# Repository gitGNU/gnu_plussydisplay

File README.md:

# Plussy Display Introduction

This repository contains free software and hardware design components for a small LED matrix resembling FSFE's plussy mascot. It is intended to be used, e.g., as an eyecatcher for fellowship events.

## License Information

All files in this project (except some configuration files where stated in their header) are licensed under the GPLv3 license as stated in the next section (GPLv3 License Statement).

## GPLv3 License Statement

Plussy Display
Copyright (C) 2015  Christian Carlowitz <chca@cmesh.de>

This program is free software: you can redistribute it and/or modify
it under the terms of the GNU General Public License as published by
the Free Software Foundation, either version 3 of the License, or
(at your option) any later version.

This program is distributed in the hope that it will be useful,
but WITHOUT ANY WARRANTY; without even the implied warranty of
MERCHANTABILITY or FITNESS FOR A PARTICULAR PURPOSE.  See the
GNU General Public License for more details.

You should have received a copy of the GNU General Public License
along with this program.  If not, see <http://www.gnu.org/licenses/>.

# Usage
## Adding new animations

* install dependencies for simulator (gcc, make, python2.7 including development headers, python-pygame)
* add new animation file in _uc/src/animations_, e.g., by copying an existing file
* rename animation function to match file name
* register animation function in _common.h_ for microcontroller (add declaration and _animTable_ entry)
* run `make ANIM=anim_funcname` in folder _sim_ to test

## Compiling microcontroller code

* install dependencies (gcc-arm-embedded from https://launchpad.net/gcc-arm-embedded, openocd, make)
* get libopencm3 (run `git submodule init`, enter _uc/libopencm3_, run `make`)
* run `make` or `make V=1` (verbose) in folder _uc_

## Flashing microcontroller

* find out openocd name for your JTAG adapter
* change parameter _OOCD_INTERFACE_ in file _uc/libopencm3.target.mk_ accordingly
* run `make flash` or `make flash V=1` (verbose) in folder _uc_

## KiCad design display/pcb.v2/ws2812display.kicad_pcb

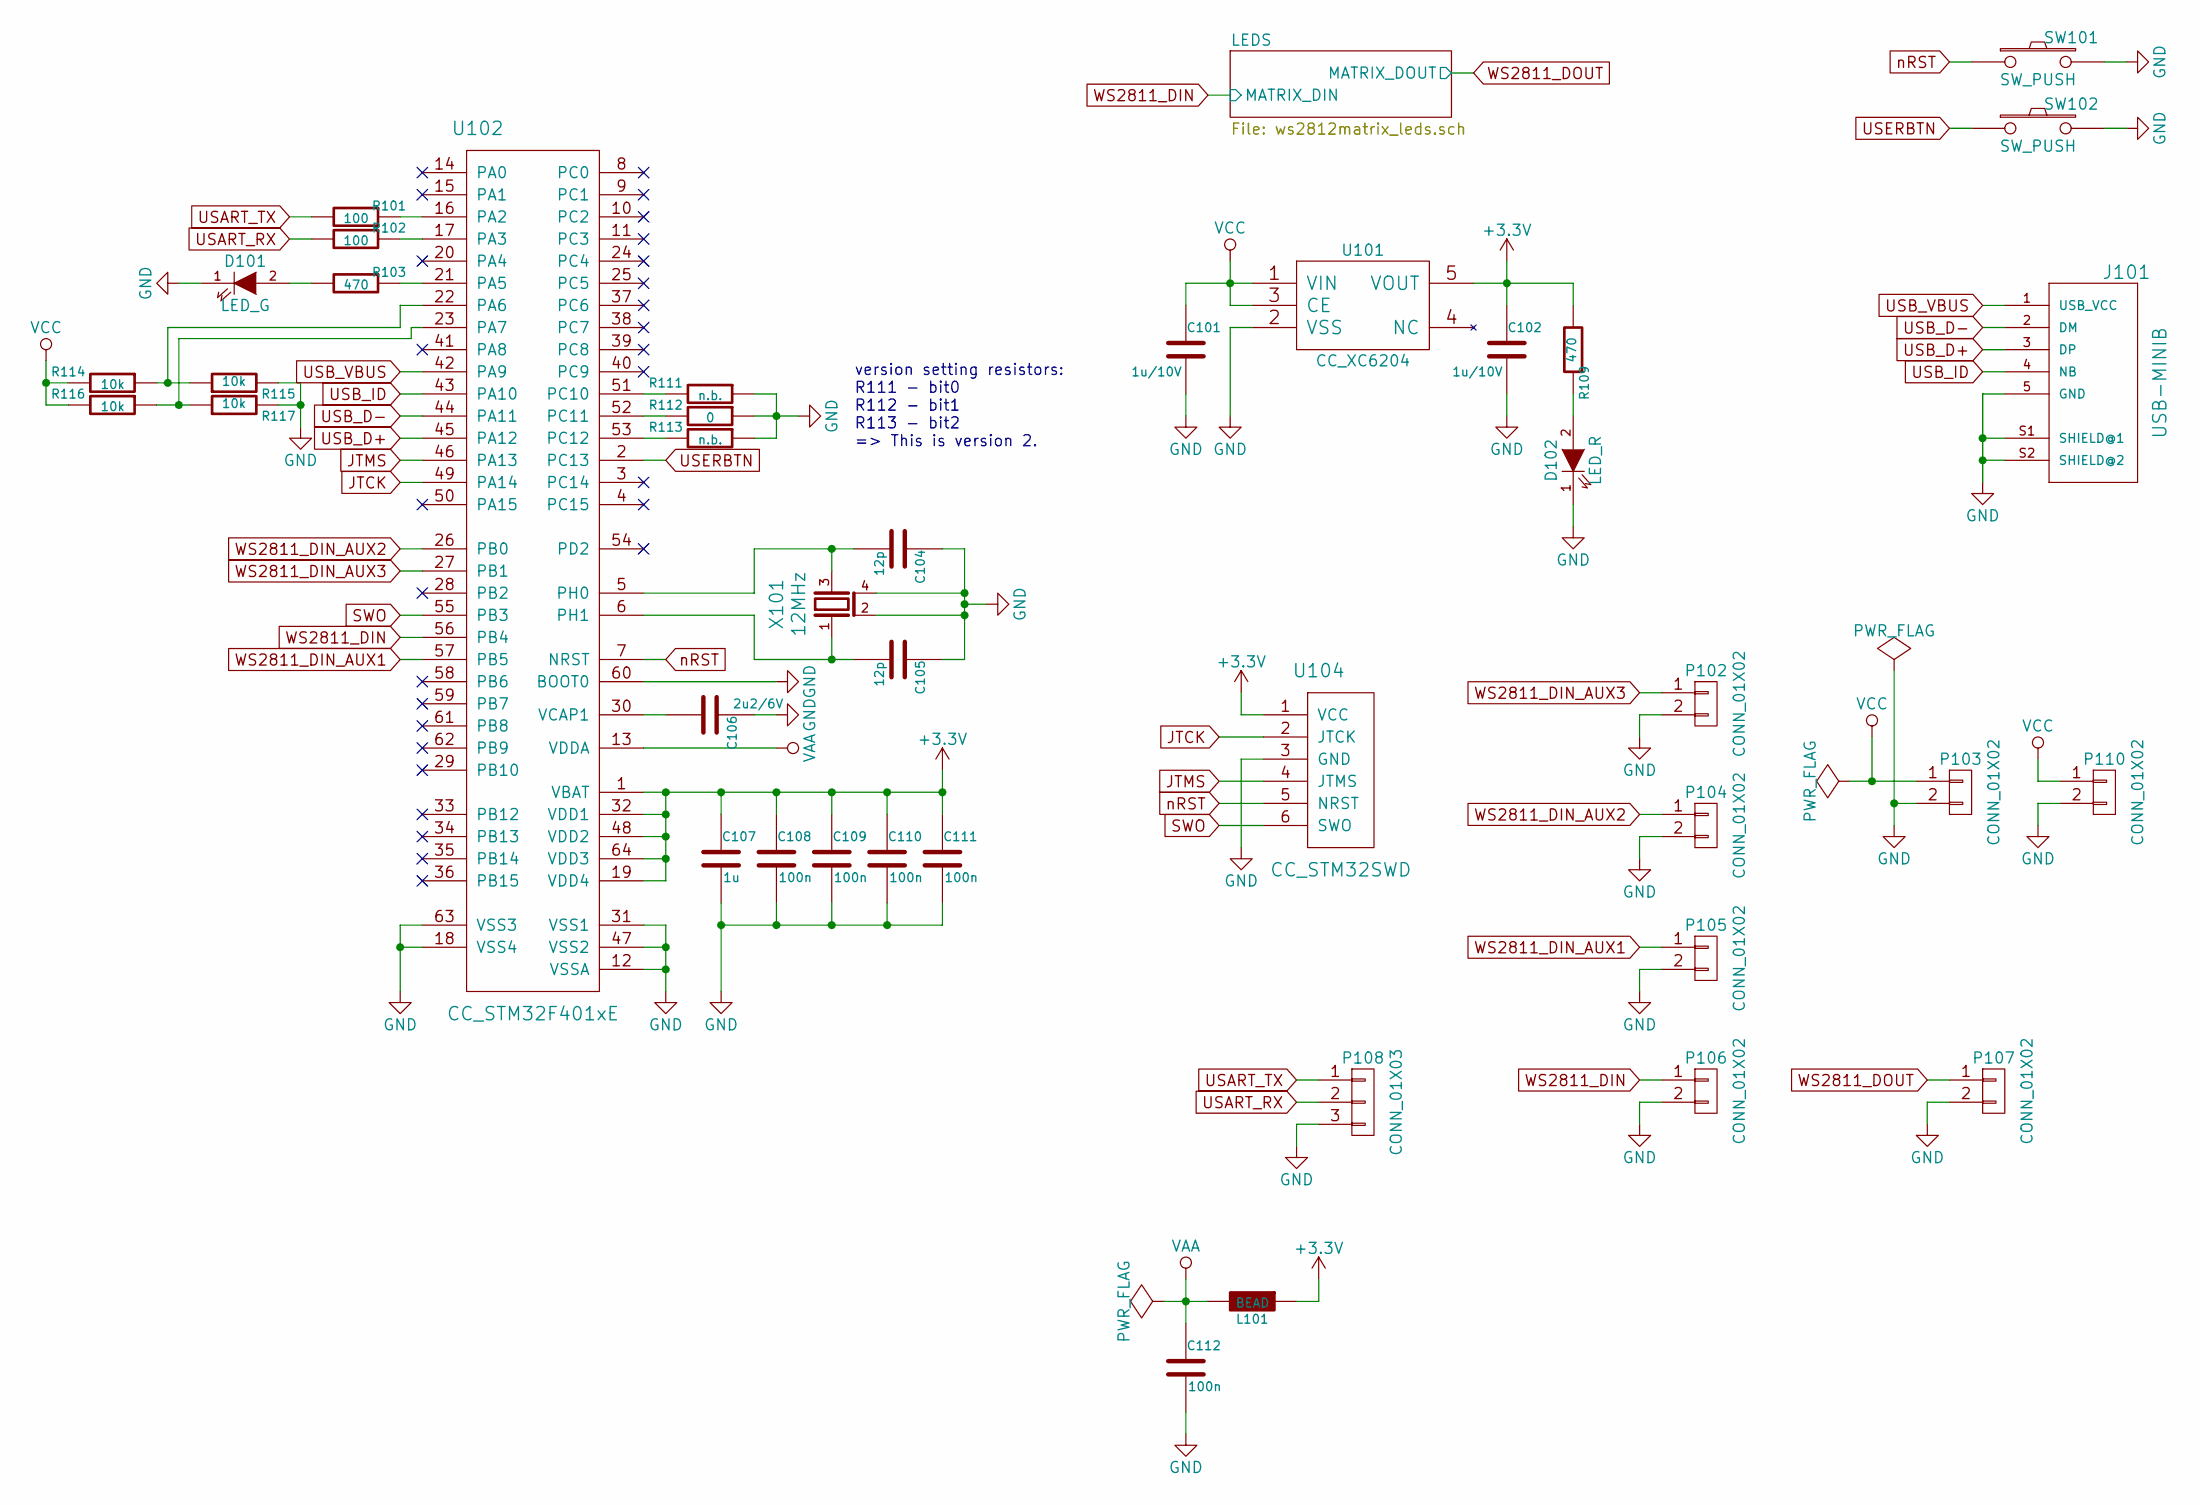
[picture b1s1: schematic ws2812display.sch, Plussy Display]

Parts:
C101, C102: 1u/10V; rcl-cc-0603
C104, C105: 12p; rcl-cc-0603
C106: 2u2/6V; rcl-cc-0603
C107: 1u; rcl-cc-0603
C108, C109, C110, C111, C112: 100n; rcl-cc-0603
D101: LED_G; LED-0603
D102: LED_R; LED-0603
J101: USB-MINIB; con-usb-USB-B-MINI-THD
L101: BEAD; rcl-cc-0603
P102, P104, P105, P106, P107: CONN_01X02; Pin_Header_Straight_1x02
P103, P110: CONN_01X02; con-ria-TYPE_230_249_2PIN
P108: CONN_01X03; Pin_Header_Straight_1x03
R101, R102: 100; rcl-cc-0603
R103, R109: 470; rcl-cc-0603
R111, R113: n.b.; rcl-cc-0603
R112: 0; rcl-cc-0603
R114, R115, R116, R117: 10k; rcl-cc-0603
SW101, SW102: SW_PUSH; TASTER_3305B
U101: CC_XC6204; SOT23-5
U102: CC_STM32F401xE; lqfp64
U104: CC_STM32SWD; Pin_Header_Straight_1x06
X101: 12MHz; Q_EUROQUARTZ_MJ_3x5x1

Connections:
+3V3: C102.1, C107.1, C108.1, C109.1, C110.1, C111.1, L101.1, R109.2, U101.5 (VOUT), U102.1 (VBAT), U102.19 (VDD4), U102.32 (VDD1), U102.48 (VDD2), U102.64 (VDD3), U104.1 (VCC)
GND: C101.2, C102.2, C104.1, C105.1, C106.1, C107.2, C108.2, C109.2, C110.2, C111.2, C112.2, D101.1 (K), D102.1 (K), J101.5 (GND), J101.S1 (SHIELD@1), J101.S2 (SHIELD@2), P102.2, P103.2, P104.2, P105.2, P106.2, P107.2, P108.3, P110.2, R111.1, R112.1, R113.1, R115.2, R117.2, SW101.2, SW102.2, U101.2 (VSS), U102.12 (VSSA), U102.18 (VSS4), U102.31 (VSS1), U102.47 (VSS2), U102.60 (BOOT0), U102.63 (VSS3), U104.3 (GND), X101.2 (GND), X101.4 (GND); also elsewhere on the board
JTCK: U102.49 (PA14), U104.2 (JTCK)
JTMS: U102.46 (PA13), U104.4 (JTMS)
unnamed: C104.2, U102.5 (PH0), X101.3
unnamed: C105.2, U102.6 (PH1), X101.1
unnamed: C106.2, U102.30 (VCAP1)
unnamed: D101.2 (A), R103.2
unnamed: D102.2 (A), R109.1
unnamed: R101.1, U102.16 (PA2)
unnamed: R102.1, U102.17 (PA3)
unnamed: R103.1, U102.21 (PA5)
unnamed: R111.2, U102.51 (PC10)
unnamed: R112.2, U102.52 (PC11)
unnamed: R113.2, U102.53 (PC12)
unnamed: R114.1, R115.1, U102.22 (PA6)
unnamed: R116.1, R117.1, U102.23 (PA7)
SWO: U102.55 (PB3), U104.6 (SWO)
USART_RX: P108.2, R102.2
USART_TX: P108.1, R101.2
USB_D+: J101.3 (DP), U102.45 (PA12)
USB_D-: J101.2 (DM), U102.44 (PA11)
USB_ID: J101.4 (NB), U102.43 (PA10)
USB_VBUS: J101.1 (USB_VCC), U102.42 (PA9)
USERBTN: SW102.1, U102.2 (PC13)
VAA: C112.1, L101.2, U102.13 (VDDA)
VCC: C101.1, P103.1, P110.1, R114.2, R116.2, U101.1 (VIN), U101.3 (CE); also elsewhere on the board
WS2811_DIN: P106.1, U102.56 (PB4); also elsewhere on the board
WS2811_DIN_AUX1: P105.1, U102.57 (PB5)
WS2811_DIN_AUX2: P104.1, U102.26 (PB0)
WS2811_DIN_AUX3: P102.1, U102.27 (PB1)
WS2811_DOUT: P107.1; also elsewhere on the board
nRST: SW101.1, U102.7 (NRST), U104.5 (NRST)

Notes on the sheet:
version setting resistors: R111 - bit0 R112 - bit1 R113 - bit2 => This is version 2.

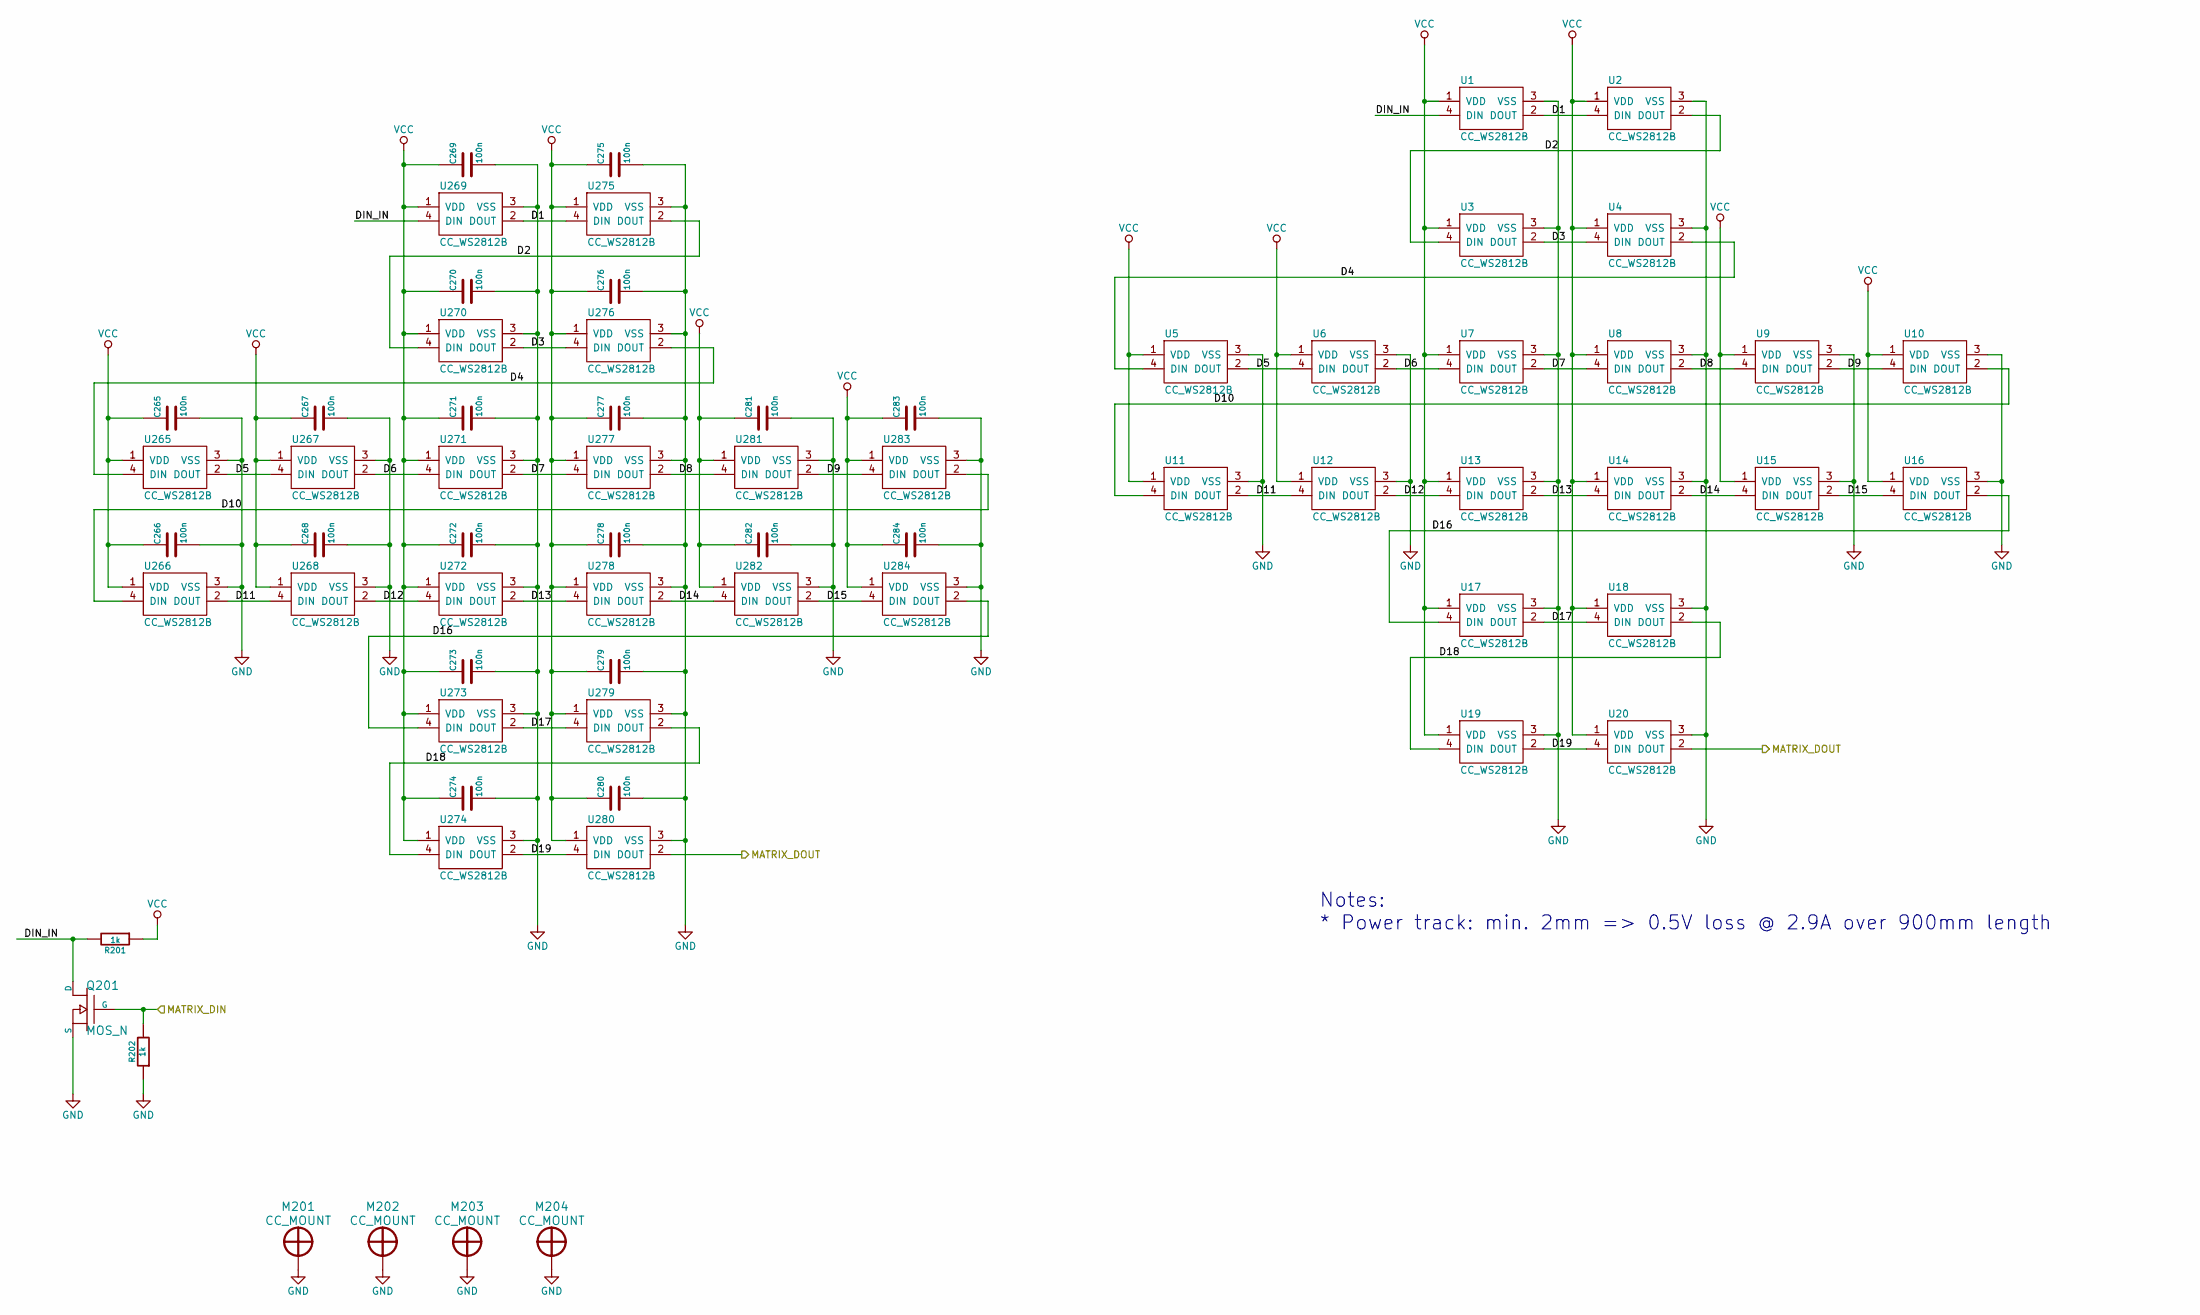
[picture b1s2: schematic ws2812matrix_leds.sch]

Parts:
C265, C266, C267, C268, C269, C270, C271, C272, C273, C274, C275, C276, C277, C278, C279, C280, C281, C282, C283, C284: 100n; rcl-cc-0603
M201, M202, M203, M204: CC_MOUNT; CC_MOUNT_PLATED_M3
Q201: MOS_N; CC_SOT23_MOS1
R201, R202: 1k; rcl-cc-0603
U1, U2, U3, U4, U5, U6, U7, U8, U9, U10, U11, U12, U13, U14, U15, U16, U17, U18, U19, U20: CC_WS2812B; WS2812B
U265, U266, U267, U268, U269, U270, U271, U272, U273, U274, U275, U276, U277, U278, U279, U280, U281, U282, U283, U284: CC_WS2812B; WS2812B_DUAL

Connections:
/LEDS/D1: U1.2 (DOUT), U2.4 (DIN), U269.2 (DOUT), U275.4 (DIN)
/LEDS/D2: U2.2 (DOUT), U3.4 (DIN), U270.4 (DIN), U275.2 (DOUT)
/LEDS/D3: U3.2 (DOUT), U4.4 (DIN), U270.2 (DOUT), U276.4 (DIN)
/LEDS/D4: U4.2 (DOUT), U5.4 (DIN), U265.4 (DIN), U276.2 (DOUT)
/LEDS/D5: U5.2 (DOUT), U6.4 (DIN), U265.2 (DOUT), U267.4 (DIN)
/LEDS/D6: U6.2 (DOUT), U7.4 (DIN), U267.2 (DOUT), U271.4 (DIN)
/LEDS/D7: U7.2 (DOUT), U8.4 (DIN), U271.2 (DOUT), U277.4 (DIN)
/LEDS/D8: U8.2 (DOUT), U9.4 (DIN), U277.2 (DOUT), U281.4 (DIN)
/LEDS/D9: U9.2 (DOUT), U10.4 (DIN), U281.2 (DOUT), U283.4 (DIN)
/LEDS/D10: U10.2 (DOUT), U11.4 (DIN), U266.4 (DIN), U283.2 (DOUT)
/LEDS/D11: U11.2 (DOUT), U12.4 (DIN), U266.2 (DOUT), U268.4 (DIN)
/LEDS/D12: U12.2 (DOUT), U13.4 (DIN), U268.2 (DOUT), U272.4 (DIN)
/LEDS/D13: U13.2 (DOUT), U14.4 (DIN), U272.2 (DOUT), U278.4 (DIN)
/LEDS/D14: U14.2 (DOUT), U15.4 (DIN), U278.2 (DOUT), U282.4 (DIN)
/LEDS/D15: U15.2 (DOUT), U16.4 (DIN), U282.2 (DOUT), U284.4 (DIN)
/LEDS/D16: U16.2 (DOUT), U17.4 (DIN), U273.4 (DIN), U284.2 (DOUT)
/LEDS/D17: U17.2 (DOUT), U18.4 (DIN), U273.2 (DOUT), U279.4 (DIN)
/LEDS/D18: U18.2 (DOUT), U19.4 (DIN), U274.4 (DIN), U279.2 (DOUT)
/LEDS/D19: U19.2 (DOUT), U20.4 (DIN), U274.2 (DOUT), U280.4 (DIN)
/LEDS/DIN_IN: Q201.D, R201.2, U1.4 (DIN), U269.4 (DIN)
GND: C265.2, C266.2, C267.2, C268.2, C269.2, C270.2, C271.2, C272.2, C273.2, C274.2, C275.2, C276.2, C277.2, C278.2, C279.2, C280.2, C281.2, C282.2, C283.2, C284.2, M201.1, M202.1, M203.1, M204.1, Q201.S, R202.1, U1.3 (VSS), U2.3 (VSS), U3.3 (VSS), U4.3 (VSS), U5.3 (VSS), U6.3 (VSS), U7.3 (VSS), U8.3 (VSS), U9.3 (VSS), U10.3 (VSS), U11.3 (VSS), U12.3 (VSS), U13.3 (VSS), U14.3 (VSS), U15.3 (VSS), U16.3 (VSS), U17.3 (VSS), U18.3 (VSS), U19.3 (VSS), U20.3 (VSS), U265.3 (VSS), U266.3 (VSS), U267.3 (VSS), U268.3 (VSS), U269.3 (VSS), U270.3 (VSS), U271.3 (VSS), U272.3 (VSS), U273.3 (VSS), U274.3 (VSS), U275.3 (VSS), U276.3 (VSS), U277.3 (VSS), U278.3 (VSS), U279.3 (VSS), U280.3 (VSS), U281.3 (VSS), U282.3 (VSS), U283.3 (VSS), U284.3 (VSS); also elsewhere on the board
VCC: C265.1, C266.1, C267.1, C268.1, C269.1, C270.1, C271.1, C272.1, C273.1, C274.1, C275.1, C276.1, C277.1, C278.1, C279.1, C280.1, C281.1, C282.1, C283.1, C284.1, R201.1, U1.1 (VDD), U2.1 (VDD), U3.1 (VDD), U4.1 (VDD), U5.1 (VDD), U6.1 (VDD), U7.1 (VDD), U8.1 (VDD), U9.1 (VDD), U10.1 (VDD), U11.1 (VDD), U12.1 (VDD), U13.1 (VDD), U14.1 (VDD), U15.1 (VDD), U16.1 (VDD), U17.1 (VDD), U18.1 (VDD), U19.1 (VDD), U20.1 (VDD), U265.1 (VDD), U266.1 (VDD), U267.1 (VDD), U268.1 (VDD), U269.1 (VDD), U270.1 (VDD), U271.1 (VDD), U272.1 (VDD), U273.1 (VDD), U274.1 (VDD), U275.1 (VDD), U276.1 (VDD), U277.1 (VDD), U278.1 (VDD), U279.1 (VDD), U280.1 (VDD), U281.1 (VDD), U282.1 (VDD), U283.1 (VDD), U284.1 (VDD); also elsewhere on the board
WS2811_DIN: Q201.G, R202.2; also elsewhere on the board
WS2811_DOUT: U20.2 (DOUT), U280.2 (DOUT); also elsewhere on the board

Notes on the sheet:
Notes: * Power track: min. 2mm => 0.5V loss @ 2.9A over 900mm length

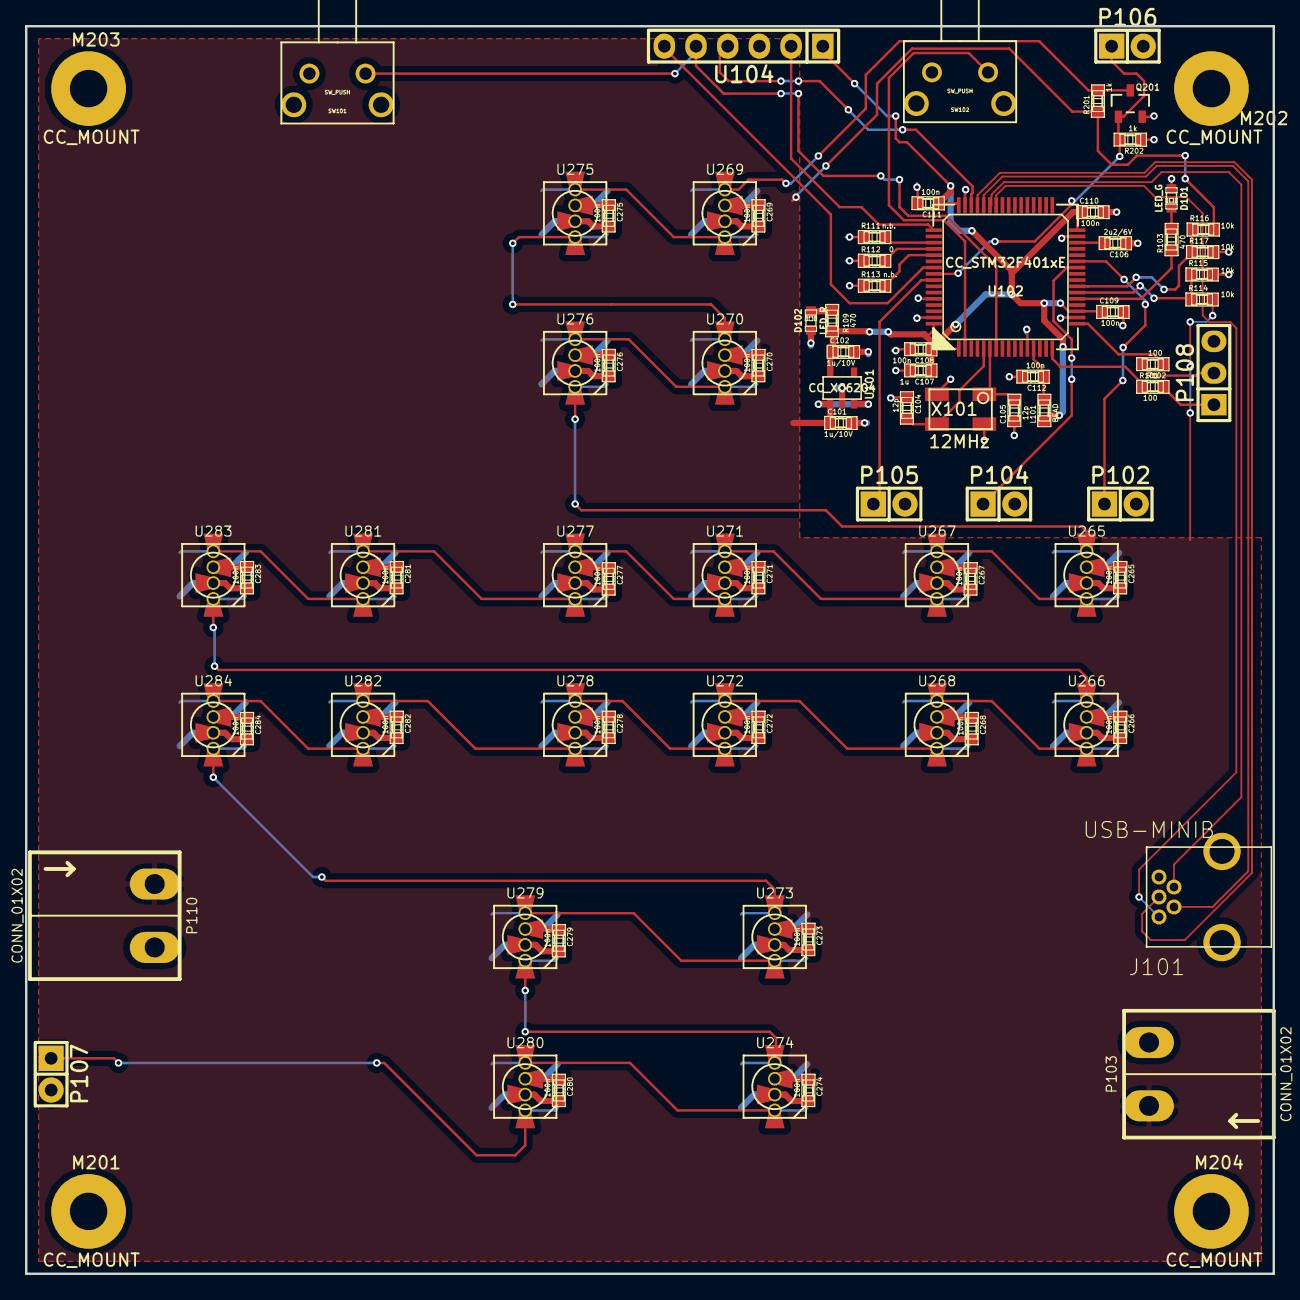
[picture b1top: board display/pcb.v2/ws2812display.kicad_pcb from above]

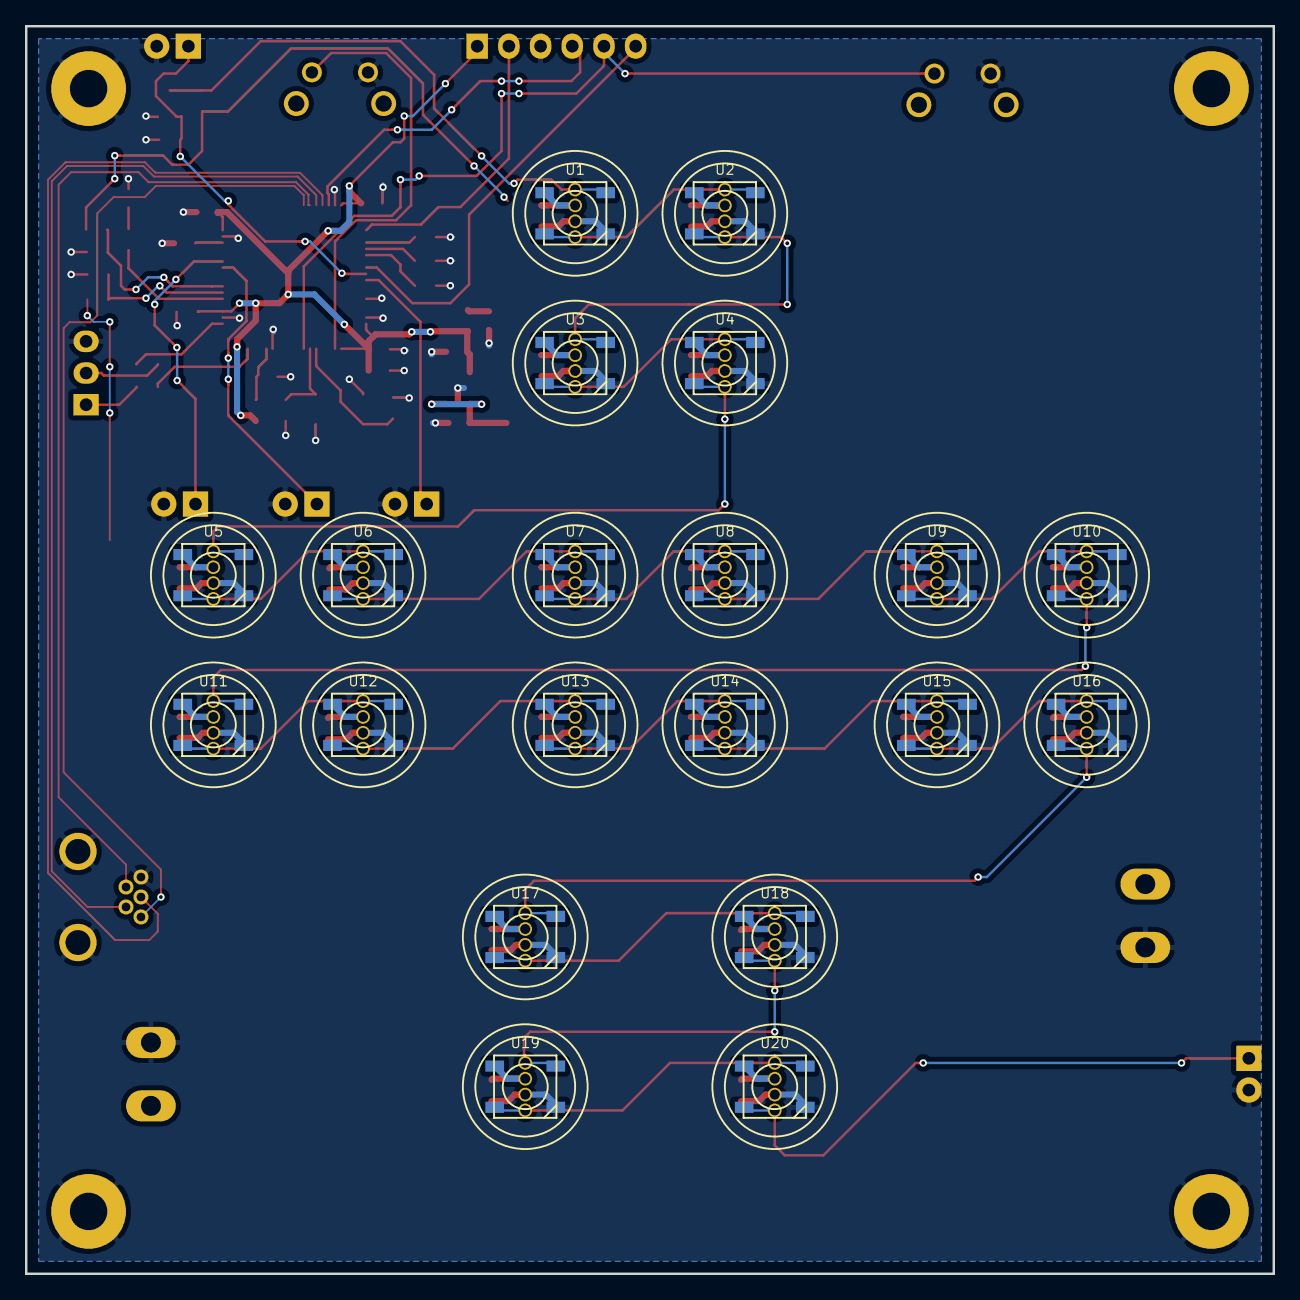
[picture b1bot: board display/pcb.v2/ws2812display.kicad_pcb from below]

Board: 2 copper layers, 100.0 x 100.0 mm, 107 parts (20 on the bottom side), 53 nets.

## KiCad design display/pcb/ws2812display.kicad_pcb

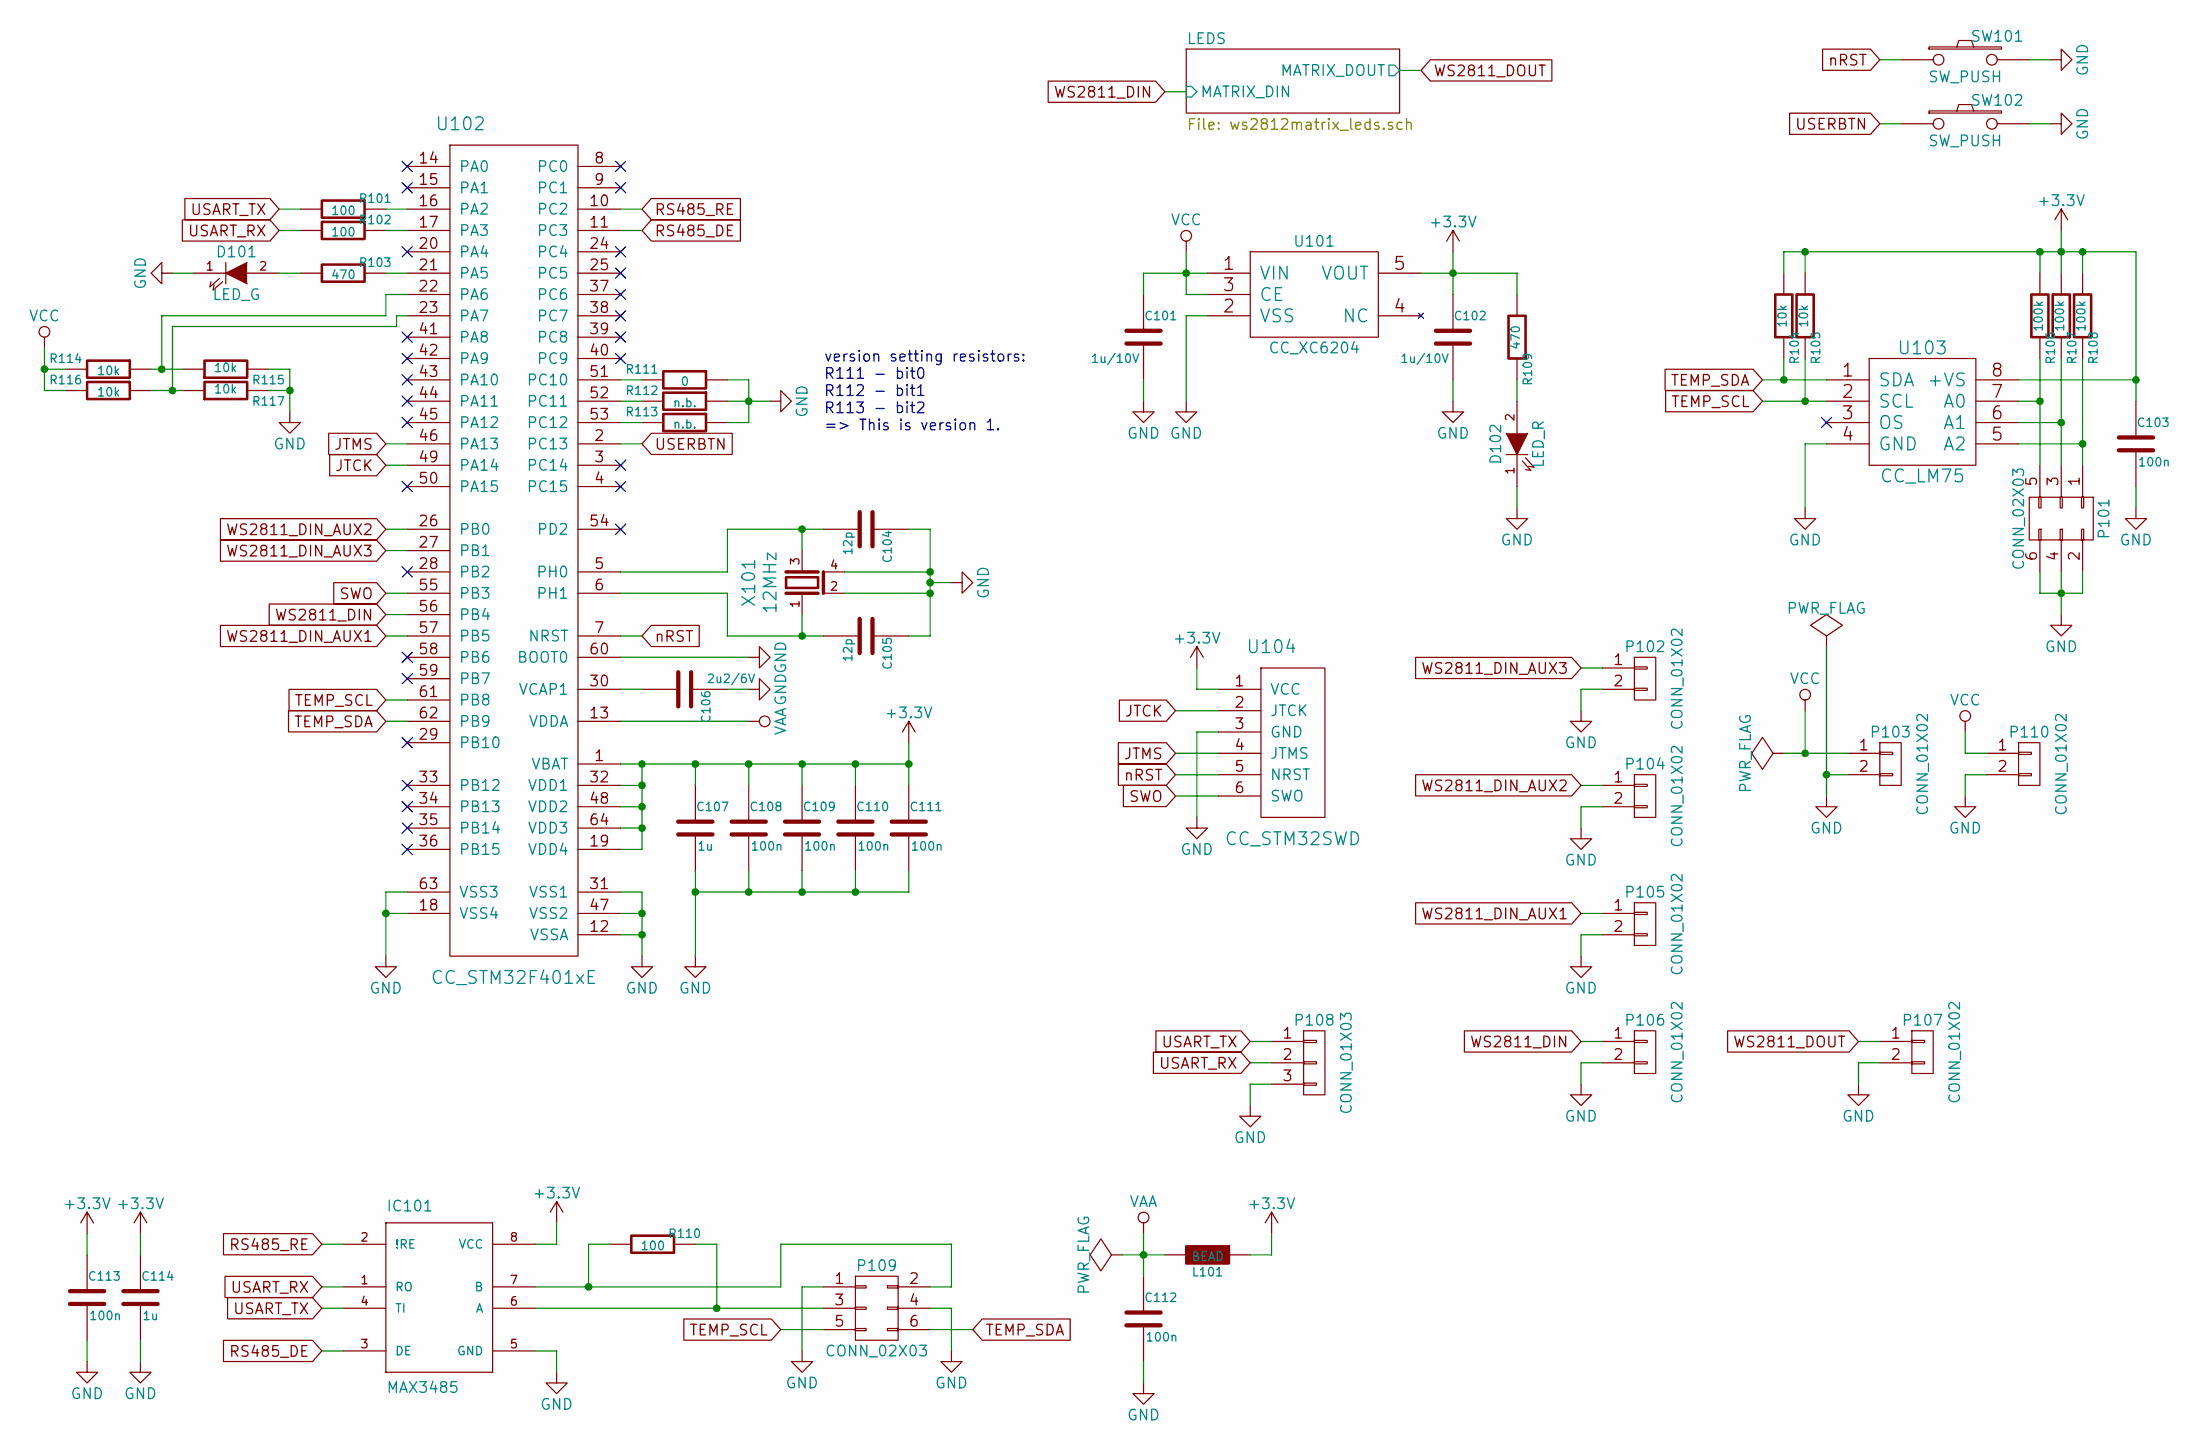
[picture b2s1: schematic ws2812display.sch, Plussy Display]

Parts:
C101, C102: 1u/10V; rcl-cc-0603
C103, C108, C109, C110, C111, C112, C113: 100n; rcl-cc-0603
C104, C105: 12p; rcl-cc-0603
C106: 2u2/6V; rcl-cc-0603
C107, C114: 1u; rcl-cc-0603
D101: LED_G; LED-0603
D102: LED_R; LED-0603
IC101: MAX3485; if-driver-SO08
L101: BEAD; rcl-cc-0603
P101: CONN_02X03; Pin_Header_Straight_2x03
P102, P104, P105, P106, P107: CONN_01X02; Pin_Header_Straight_1x02
P103, P110: CONN_01X02; con-ria-TYPE_230_249_2PIN
P108: CONN_01X03; Pin_Header_Straight_1x03
P109: CONN_02X03; con-harting-ml-ML6
R101, R102, R110: 100; rcl-cc-0603
R103, R109: 470; rcl-cc-0603
R104, R105, R114, R115, R116, R117: 10k; rcl-cc-0603
R106, R107, R108: 100k; rcl-cc-0603
R111: 0; rcl-cc-0603
R112, R113: n.b.; rcl-cc-0603
SW101, SW102: SW_PUSH; TASTER_3305B
U101: CC_XC6204; SOT23-5
U102: CC_STM32F401xE; lqfp64
U103: CC_LM75; SOIC-8_N
U104: CC_STM32SWD; Pin_Header_Straight_1x06
X101: 12MHz; Q_EUROQUARTZ_MJ_3x5x1

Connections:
+3V3: C102.1, C103.1, C107.1, C108.1, C109.1, C110.1, C111.1, C113.1, C114.1, IC101.8 (VCC), L101.1, R104.2, R105.2, R106.2, R107.2, R108.2, R109.2, U101.5 (VOUT), U102.1 (VBAT), U102.19 (VDD4), U102.32 (VDD1), U102.48 (VDD2), U102.64 (VDD3), U103.8 (+VS), U104.1 (VCC)
GND: C101.2, C102.2, C103.2, C104.1, C105.1, C106.1, C107.2, C108.2, C109.2, C110.2, C111.2, C112.2, C113.2, C114.2, D101.1 (K), D102.1 (K), IC101.5 (GND), P101.2, P101.4, P101.6, P102.2, P103.2, P104.2, P105.2, P106.2, P107.2, P108.3, P109.1, P109.4, P110.2, R111.1, R112.1, R113.1, R115.2, R117.2, SW101.2, SW102.2, U101.2 (VSS), U102.12 (VSSA), U102.18 (VSS4), U102.31 (VSS1), U102.47 (VSS2), U102.60 (BOOT0), U102.63 (VSS3), U103.4 (GND), U104.3 (GND), X101.2 (GND), X101.4 (GND); also elsewhere on the board
JTCK: U102.49 (PA14), U104.2 (JTCK)
JTMS: U102.46 (PA13), U104.4 (JTMS)
unnamed: C104.2, U102.5 (PH0), X101.3
unnamed: C105.2, U102.6 (PH1), X101.1
unnamed: C106.2, U102.30 (VCAP1)
unnamed: D101.2 (A), R103.2
unnamed: D102.2 (A), R109.1
unnamed: IC101.6 (A), P109.3, R110.1
unnamed: IC101.7 (B), P109.2, R110.2
unnamed: P101.1, R108.1, U103.5 (A2)
unnamed: P101.3, R107.1, U103.6 (A1)
unnamed: P101.5, R106.1, U103.7 (A0)
unnamed: R101.1, U102.16 (PA2)
unnamed: R102.1, U102.17 (PA3)
unnamed: R103.1, U102.21 (PA5)
unnamed: R111.2, U102.51 (PC10)
unnamed: R112.2, U102.52 (PC11)
unnamed: R113.2, U102.53 (PC12)
unnamed: R114.1, R115.1, U102.22 (PA6)
unnamed: R116.1, R117.1, U102.23 (PA7)
RS485_DE: IC101.3 (DE), U102.11 (PC3)
RS485_RE: IC101.2 (!RE), U102.10 (PC2)
SWO: U102.55 (PB3), U104.6 (SWO)
TEMP_SCL: P109.5, R105.1, U102.61 (PB8), U103.2 (SCL)
TEMP_SDA: P109.6, R104.1, U102.62 (PB9), U103.1 (SDA)
USART_RX: IC101.1 (RO), P108.2, R102.2
USART_TX: IC101.4 (TI), P108.1, R101.2
USERBTN: SW102.1, U102.2 (PC13)
VAA: C112.1, L101.2, U102.13 (VDDA)
VCC: C101.1, P103.1, P110.1, R114.2, R116.2, U101.1 (VIN), U101.3 (CE); also elsewhere on the board
WS2811_DIN: P106.1, U102.56 (PB4); also elsewhere on the board
WS2811_DIN_AUX1: P105.1, U102.57 (PB5)
WS2811_DIN_AUX2: P104.1, U102.26 (PB0)
WS2811_DIN_AUX3: P102.1, U102.27 (PB1)
WS2811_DOUT: P107.1; also elsewhere on the board
nRST: SW101.1, U102.7 (NRST), U104.5 (NRST)

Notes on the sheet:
version setting resistors: R111 - bit0 R112 - bit1 R113 - bit2 => This is version 1.

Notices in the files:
display/pcb.v2/ws2812display.kicad_pcb:
LICENSE: GNU GPLv3
display/pcb.v2/ws2812display.sch:
http://www.gnu.org/licenses/gpl-3.0.txt
